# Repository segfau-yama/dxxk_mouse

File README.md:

# dxxk_mouse

ESP32-S3 上で動作する Rust 製 USB 入力デバイスの実験用リポジトリです。

ファームウェアは、USB HID のキーボードとマウス、USB Audio Class 1（UAC1）のマイクとスピーカーを一つの USB デバイスとして提供します。

## 対象環境

| 項目 | 構成 |
| --- | --- |
| MCU | ESP32-S3 |
| Rust target | `xtensa-esp32s3-none-elf` |
| HAL | `esp-hal` |
| async runtime | Embassy、`esp-rtos` |
| USB | `embassy-usb` |
| 実機テスト | `embedded-test`、`probe-rs` |

## ディレクトリ構成

```text
dick_mouse
├── Cargo.toml
├── .cargo/config.toml
├── src
│   ├── main.rs
│   ├── lib.rs
│   ├── device
│   │   ├── button.rs
│   │   ├── encoder.rs
│   │   ├── joystick.rs
│   │   ├── microphone.rs
│   │   └── speaker.rs
│   └── tasks
│       ├── audio.rs
│       ├── hid.rs
│       ├── keyboard.rs
│       ├── mouse.rs
│       └── usb.rs
└── tests
    ├── device
    │   ├── button.rs
    │   ├── encoder.rs
    │   ├── joystick.rs
    │   ├── microphone.rs
    │   └── speaker.rs
    ├── main.rs
    ├── reexports.rs
    └── tasks
        └── mod.rs
```

## 設計図

```mermaid
flowchart TD
  subgraph Mode["mode"]
    direction TB
    UsbHidReports["CHANNEL: USB_HID_REPORTS"]
    ModeGpio["PERIPHERAL: GPIO21 slide switch"] --> HidTask["TASK: hid_task"]
  end

  subgraph Keyboard["keyboard"]
    direction TB
    ShortcutGpio["PERIPHERAL: GPIO6/7 shortcut buttons"]
    PushGpio["PERIPHERAL: GPIO42 joystick push"]
    KeyboardTask["TASK: keyboard_task"]
    KeyboardReports["CHANNEL: KEYBOARD_REPORTS"]
    ShortcutGpio --> KeyboardTask
    PushGpio --> KeyboardTask
  end

  subgraph Mouse["mouse"]
    direction TB
    ClickGpio["PERIPHERAL: GPIO38/39 click buttons"]
    JoystickAdc["PERIPHERAL: ADC1 GPIO1/2 joystick"]
    ScrollPcnt["PERIPHERAL: PCNT0 GPIO11/12 scroll encoder"]
    MouseTask["TASK: mouse_task"]
    MouseReports["CHANNEL: MOUSE_REPORTS"]
    ClickGpio --> MouseTask
    JoystickAdc --> MouseTask
    ScrollPcnt --> MouseTask
  end

  subgraph Microphone["microphone"]
    direction TB
    I2sMic["PERIPHERAL: I2S0 RX microphone"]
    MicMuteGpio["PERIPHERAL: GPIO4 microphone mute"]
    MicVolumePcnt["PERIPHERAL: PCNT1 GPIO13/14 volume encoder"]
    MicrophoneTask["TASK: microphone_task"]
    MicrophoneFrames["SPSC: MICROPHONE_RING"]
    I2sMic --> MicrophoneTask
    MicMuteGpio --> MicrophoneTask
    MicVolumePcnt --> MicrophoneTask
    MicrophoneTask --> MicrophoneFrames
  end

  subgraph Speaker["speaker"]
    direction TB
    SpeakerFrames["SPSC: SPEAKER_RING"]
    SpeakerMuteGpio["PERIPHERAL: GPIO5 speaker mute"]
    SpeakerVolumePcnt["PERIPHERAL: PCNT2 GPIO40/41 volume encoder"]
    SpeakerTask["TASK: speaker_task"]
    I2sSpeaker["PERIPHERAL: I2S0 TX speaker"]
    SpeakerFrames --> SpeakerTask
    SpeakerMuteGpio --> SpeakerTask
    SpeakerVolumePcnt --> SpeakerTask
    SpeakerTask --> I2sSpeaker
  end

  UsbTask["TASK: usb_task"]

  subgraph Usb["usb"]
    direction LR
    UsbHid["USB: HID keyboard / mouse"]
    UsbMic["USB: UAC microphone"]
    UsbSpeaker["USB: UAC speaker"]
    UsbPeripheral["PERIPHERAL: USB0 GPIO19/20"]
    UsbHid --> UsbPeripheral
    UsbMic --> UsbPeripheral
    UsbPeripheral --> UsbSpeaker
  end

  UsbTask --> UsbHid
  UsbTask --> UsbMic
  UsbSpeaker --> UsbTask

  KeyboardTask --> KeyboardReports
  MouseTask --> MouseReports
  KeyboardReports --> HidTask
  MouseReports --> HidTask
  HidTask --> UsbHidReports
  UsbHidReports --> UsbTask
  MicrophoneFrames --> UsbTask
  UsbTask --> SpeakerFrames

  class ShortcutGpio,PushGpio,ModeGpio,ClickGpio,JoystickAdc,ScrollPcnt,MicMuteGpio,MicVolumePcnt,I2sMic,SpeakerMuteGpio,SpeakerVolumePcnt,I2sSpeaker,UsbPeripheral peripheral
  class KeyboardTask,HidTask,MouseTask,MicrophoneTask,SpeakerTask,UsbTask task
  class KeyboardReports,MouseReports,UsbHidReports,MicrophoneFrames,SpeakerFrames channel
  class UsbHid,UsbMic,UsbSpeaker usb

  classDef peripheral fill:#ddf4ff,stroke:#0969da,color:#24292f
  classDef task fill:#dafbe1,stroke:#1a7f37,color:#24292f
  classDef channel fill:#fff8c5,stroke:#9a6700,color:#24292f
  classDef usb fill:#fbefff,stroke:#8250df,color:#24292f
```

## 実装概要

### デバイス状態

| 型 | 入力 | 責務 |
| --- | --- | --- |
| `Button` | GPIO level、時刻 | active level、debounce、押下状態を保持する |
| `RotaryEncoder` | PCNT count、時刻 | count を安定化し、detent 算出に使う値を保持する |
| `Joystick` | X/Y の ADC 値 | 初期位置を中心として X/Y の差分を計算する |
| `Microphone` | I2S RX frame | USB マイクへ送る音声フレームを保持する |
| `Speaker` | USB speaker frame | I2S TX へ送る音声フレームを保持する |

各構造体は setter や `&mut self` を持たず、`update(self) -> Self` または `new()` で新しい状態を返します。

### task のデータフロー

USB HID と USB Audio は、同じ列で入力、処理、出力を示します。

#### USB HID

| task | 入力 | 処理 | 出力 |
| --- | --- | --- | --- |
| `keyboard_task` | joystick push、Back、Forward の GPIO | `Button` を更新し、ボタン状態を集約する | `KEYBOARD_REPORTS` |
| `mouse_task` | click の GPIO、joystick の ADC、encoder の PCNT | `Button`、`Joystick`、`RotaryEncoder` を更新し、マウス入力を集約する | `MOUSE_REPORTS` |
| `hid_task` | mode GPIO、`KEYBOARD_REPORTS`、`MOUSE_REPORTS` | mode に応じて入力を keyboard または mouse report に変換する | `USB_HID_REPORTS` |
| `usb_task` | `USB_HID_REPORTS` | report ID を付けて HID endpoint へ書き込む | USB HID keyboard、mouse |

#### USB Audio

| task | 入力 | 処理 | 出力 |
| --- | --- | --- | --- |
| `microphone_task` | I2S RX、mute GPIO、volume encoder の PCNT | DMAを常時drainし、muteと音量を反映したmono S16を格納する | `MICROPHONE_RING` |
| `usb_task`（microphone） | `MICROPHONE_RING` | リングを待たずに47/48/49 sampleのmono packetを組み立てる | USB UAC1 microphone |
| `usb_task`（speaker） | USB UAC1 speaker | mono S16を格納し、USB mute/volumeも監視する | `SPEAKER_RING` |
| `speaker_task` | `SPEAKER_RING`、mute GPIO、volume encoder の PCNT | USBと物理入力のmute/volumeを反映し、連続DMAへstereo S32を補充する | I2S TX |

## 入力割り当て

`GPIO21` のスライドスイッチに応じて、`hid_task` が通常モードとゲームモードを切り替えます。

| 入力 | 通常モード | ゲームモード |
| --- | --- | --- |
| joystick X/Y | Mouse X/Y | Arrow keys |
| joystick push | PrintScreen | S |
| left click | Mouse left button | A |
| right click | Mouse right button | D |
| Back button | Ctrl+Left | Space |
| Forward button | Ctrl+Right | Enter |
| scroll encoder | Mouse wheel | 使用しない |

ゲームモードでは joystick の X/Y 差分が `512` を超えた方向をキー入力へ変換します。

同時押しが HID keyboard の上限を超えた場合は、実装上の割り当て順で先頭の 6 キーを送信します。

## USB インターフェース

| インターフェース | USB class | 方向 | データ形式 |
| --- | --- | --- | --- |
| Keyboard | HID、report ID `1` | ESP32-S3 から PC | modifier、6 keycodes |
| Mouse | HID、report ID `2` | ESP32-S3 から PC | buttons、X/Y、wheel、pan |
| Microphone | UAC1 source | ESP32-S3 から PC | 48 kHz、16-bit、mono、単一IN、feedbackなし |
| Speaker | UAC1 speaker | PC から ESP32-S3 | 48 kHz、16-bit、mono（Left Front） |

I2S は RX、TX ともに 48 kHz、32-bit slot で動作します。
RX はINMP441の左スロットだけをDMAへ取り込み、符号付き24-bitから16-bit PCMへ変換します（L/R端子はLow）。
TX はUSBのmono S16を32-bitの上位16 bitへ配置し、左右両スロットへ複製します。
マイクは未実装のUSB音量制御を広告せず、スピーカーはUSBのmute/volumeと物理ボタンをPCMへ反映します。
音声にはheaplessのSPSCキューを使用し、USB/I2S処理中にUARTログを出しません。

現在の試作機の配線と再録音の確認方法は [AUDIO_CHECK.md](AUDIO_CHECK.md) を参照してください。
以下の回路設計用ピン表と試作機の `main.rs` は異なるため、配線の変更時には `main.rs` を確認してください。

## ピン割り当て

| 機能 | 信号 | peripheral | GPIO | 所有する task |
| --- | --- | --- | --- | --- |
| Mode | slide switch | GPIO | `GPIO21` | `hid_task` |
| Keyboard | joystick push | GPIO | `GPIO42` | `keyboard_task` |
| Keyboard | Back button | GPIO | `GPIO6` | `keyboard_task` |
| Keyboard | Forward button | GPIO | `GPIO7` | `keyboard_task` |
| Mouse | joystick X | ADC1 | `GPIO1` | `mouse_task` |
| Mouse | joystick Y | ADC1 | `GPIO2` | `mouse_task` |
| Mouse | scroll encoder A | PCNT0 | `GPIO11` | `mouse_task` |
| Mouse | scroll encoder B | PCNT0 | `GPIO12` | `mouse_task` |
| Mouse | left click | GPIO | `GPIO38` | `mouse_task` |
| Mouse | right click | GPIO | `GPIO39` | `mouse_task` |
| Microphone | mute button | GPIO | `GPIO4` | `microphone_task` |
| Microphone | volume encoder A | PCNT1 | `GPIO13` | `microphone_task` |
| Microphone | volume encoder B | PCNT1 | `GPIO14` | `microphone_task` |
| Microphone | BCLK | I2S0 RX | `GPIO15` | `microphone_task` |
| Microphone | WS | I2S0 RX | `GPIO16` | `microphone_task` |
| Microphone | DIN | I2S0 RX | `GPIO17` | `microphone_task` |
| Speaker | mute button | GPIO | `GPIO5` | `speaker_task` |
| Speaker | volume encoder A | PCNT2 | `GPIO40` | `speaker_task` |
| Speaker | volume encoder B | PCNT2 | `GPIO41` | `speaker_task` |
| Speaker | BCLK | I2S0 TX | `GPIO8` | `speaker_task` |
| Speaker | WS | I2S0 TX | `GPIO9` | `speaker_task` |
| Speaker | DOUT | I2S0 TX | `GPIO10` | `speaker_task` |
| USB | D- | USB0 | `GPIO19` | `usb_task` |
| USB | D+ | USB0 | `GPIO20` | `usb_task` |

I2S RX と I2S TX は `I2S0` と `DMA_CH0` を共有します。

マイクとスピーカーの音量は起動時を 100% とし、エンコーダーの 1 detent ごとに 5% ずつ、0% から 100% の範囲で変更します。

`GPIO0/3/45/46` は strapping、`GPIO43/44` は UART0、`GPIO19/20` は USB に使われるため、汎用入力には割り当てていません。

`GPIO39/40/41/42` は外部 JTAG の既定信号と重なるため、現在の入力配線と外部 JTAG は同時に使用できません。

## ビルドと書き込み

```sh
cd dick_mouse
cargo check
cargo run --release
```

通常実行時の runner は `.cargo/config.toml` に定義した `espflash flash` です。

## 実機テスト

テストはホスト PC 上の unit test ではなく、ESP32-S3 実機上で動作する `embedded-test` 形式です。

```sh
cargo test-hil
```

`cargo test-hil` は `.cargo/config.toml` の alias で、runner を `probe-rs run --chip esp32s3` に上書きします。

| test target | 検証対象 |
| --- | --- |
| `button` | debounce と押下状態 |
| `encoder` | count の安定化 |
| `joystick` | 中心位置からの X/Y 差分 |
| `microphone` | microphone frame の状態型 |
| `speaker` | speaker frame の状態型 |
| `reexports` | `device` 型の公開 API |
| `tasks` | PCM 変換、HID report 変換、task の入口 |
| `main` | firmware で使う peripheral の初期化 |

`tests/` 配下の各ファイルは `Cargo.toml` の `[[test]]` で明示し、ESP32-S3 上の結合テストとして実行します。

## 制約

- ビルドには `xtensa-esp32s3-none-elf` target に対応した Rust 環境が必要です。
- 実機テストには `probe-rs` がデバイスへアクセスできる権限が必要です。
- `embassy-usb` は UAC1 source を使うため、Embassy の git revision に固定しています。

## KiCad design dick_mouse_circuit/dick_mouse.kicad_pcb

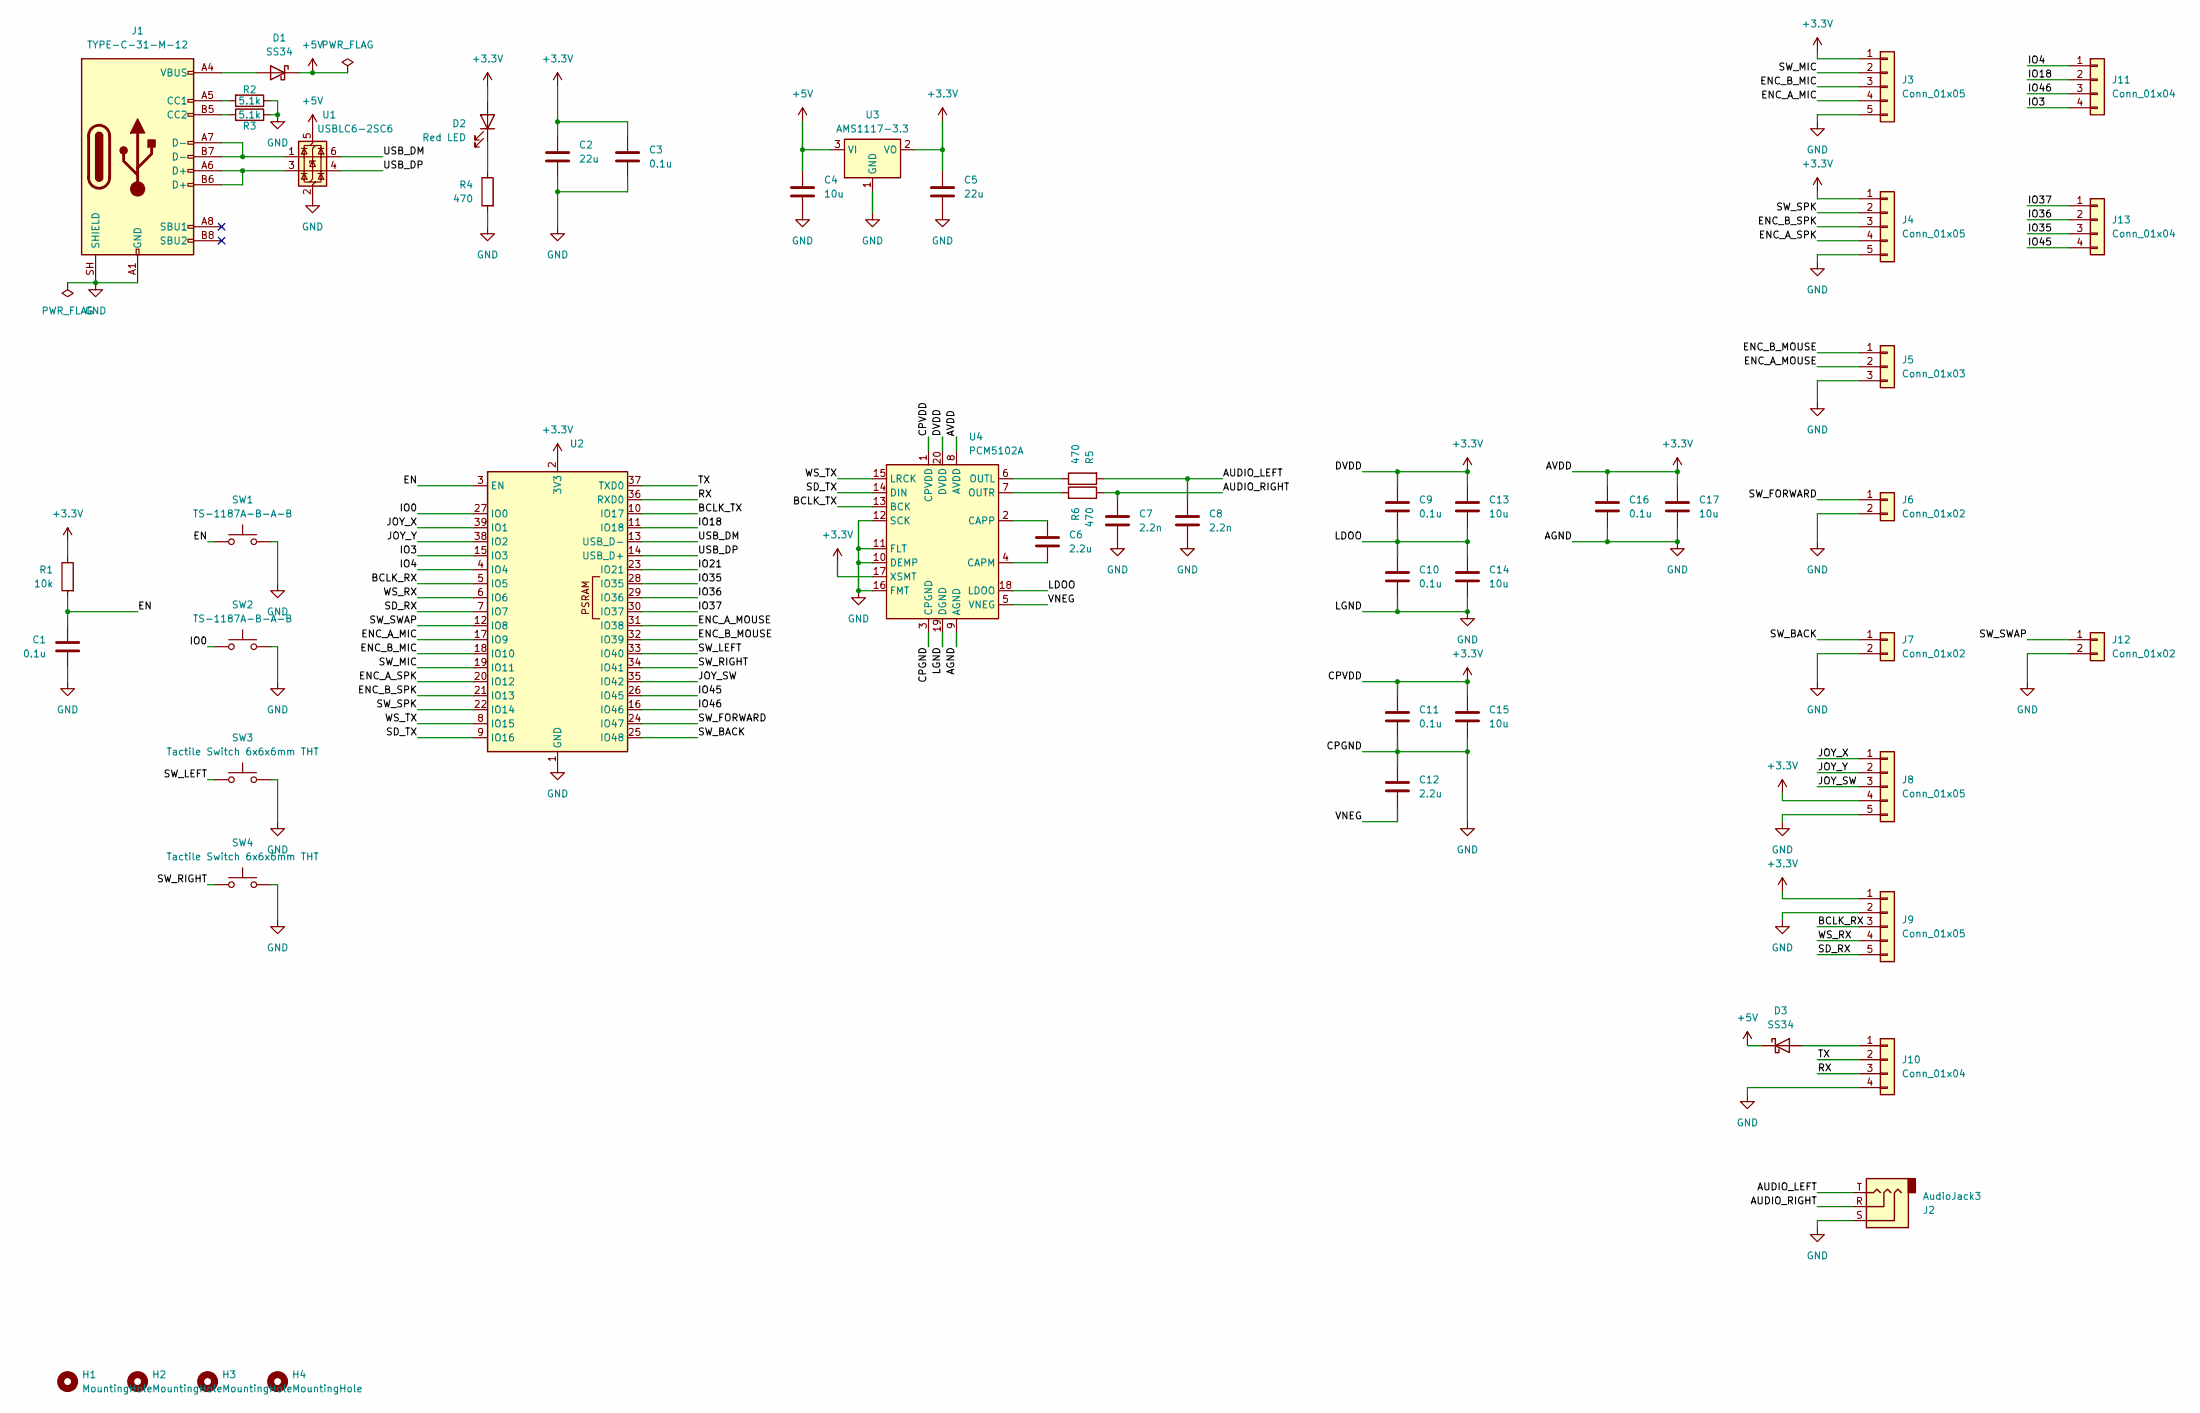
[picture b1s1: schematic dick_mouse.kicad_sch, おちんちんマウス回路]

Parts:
C1, C3, C9, C10, C11, C16: 0.1u; C_0402_1005Metric; MPN CL05B104KO5NNNC; LCSC C1525
C2, C5: 22u; C_0805_2012Metric; MPN CL21A226MAQNNNE; LCSC C45783
C4, C13, C14, C15, C17: 10u; C_0603_1608Metric; MPN CL10A106MA8NRNC; LCSC C96446
C6, C12: 2.2u; C_0402_1005Metric; MPN CL05A225MQ5NSNC; LCSC C12530
C7, C8: 2.2n; C_0402_1005Metric; MPN 0402B222K500NT; LCSC C1531
D1, D3: SS34; D_SMA; MPN SS34; LCSC C8678
D2: Red LED; LED_0603_1608Metric; MPN KT-0603R; LCSC C2286
H1, H2, H3, H4: MountingHole; MountingHole_3.2mm_M3
J1: TYPE-C-31-M-12; USB_C_Receptacle_HRO_TYPE-C-31-M-12; MPN TYPE-C-31-M-12; LCSC C165948
J2: AudioJack3; C668608_PJ-313D; MPN PJ-313D; LCSC C668608
J3, J4, J8, J9: Conn_01x05; JST_XH_B5B-XH-A_1x05_P2.50mm_Vertical; MPN PZ254V-11-05P; LCSC C492404
J5: Conn_01x03; JST_XH_B3B-XH-A_1x03_P2.50mm_Vertical; MPN PZ254V-11-03P; LCSC C2937625
J6, J7, J12: Conn_01x02; JST_XH_B2B-XH-A_1x02_P2.50mm_Vertical; MPN PZ254V-11-02P; LCSC C492401
J10, J11, J13: Conn_01x04; PinHeader_1x04_P2.54mm_Vertical; MPN PZ254V-11-04P; LCSC C2691448
R1: 10k; R_0402_1005Metric; MPN 0402WGF1002TCE; LCSC C25744
R2, R3: 5.1k; R_0402_1005Metric; MPN 0402WGF5101TCE; LCSC C25905
R4, R5, R6: 470; R_0402_1005Metric; MPN 0402WGF4700TCE; LCSC C25117
SW1, SW2: TS-1187A-B-A-B; SW_Push_1P1T_XKB_TS-1187A; MPN TS-1187A-B-A-B; LCSC C318884
SW3, SW4: Tactile Switch 6x6x6mm THT; SW_PUSH_6mm
U1: USBLC6-2SC6; SOT-23-6
U2: ESP32-S3-WROOM-1
U3: AMS1117-3.3; SOT-223-3_TabPin2; MPN AMS1117-3.3; LCSC C6186
U4: PCM5102A; TSSOP-20_4.4x6.5mm_P0.65mm

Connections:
+3.3V: C2.1, C3.1, C5.1, C9.1, C11.1, C13.1, C15.1, C16.1, C17.1, D2.2 (A), J3.1, J4.1, J8.4, J9.1, R1.1, U2.2 (3V3), U3.2 (VO), U4.1 (CPVDD), U4.8 (AVDD), U4.17 (XSMT), U4.20 (DVDD)
+5V: C4.1, D1.1 (K), D3.1 (K), U1.5 (VBUS), U3.3 (VI)
/AUDIO_LEFT: C8.1, J2.T, R5.2
/AUDIO_RIGHT: C7.1, J2.R, R6.1
/BCLK_RX: J9.3, U2.5 (IO5)
/BCLK_TX: U2.10 (IO17), U4.13 (BCK)
/EN: C1.1, R1.2, SW1.1, U2.3 (EN)
/ENC_A_MIC: J3.4, U2.17 (IO9)
/ENC_A_MOUSE: J5.2, U2.31 (IO38)
/ENC_A_SPK: J4.4, U2.20 (IO12)
/ENC_B_MIC: J3.3, U2.18 (IO10)
/ENC_B_MOUSE: J5.1, U2.32 (IO39)
/ENC_B_SPK: J4.3, U2.21 (IO13)
/IO0: SW2.1, U2.27 (IO0)
/IO3: J11.4, U2.15 (IO3)
/IO4: J11.1, U2.4 (IO4)
/IO18: J11.2, U2.11 (IO18)
/IO21: U2.23 (IO21)
/IO35: J13.3, U2.28 (IO35)
/IO36: J13.2, U2.29 (IO36)
/IO37: J13.1, U2.30 (IO37)
/IO45: J13.4, U2.26 (IO45)
/IO46: J11.3, U2.16 (IO46)
/JOY_SW: J8.3, U2.35 (IO42)
/JOY_X: J8.1, U2.39 (IO1)
/JOY_Y: J8.2, U2.38 (IO2)
/LDOO: C9.2, C10.1, C13.2, C14.1, U4.18 (LDOO)
/RX: J10.3, U2.36 (RXD0)
/SD_RX: J9.5, U2.7 (IO7)
/SD_TX: U2.9 (IO16), U4.14 (DIN)
/SW_BACK: J7.1, U2.25 (IO48)
/SW_FORWARD: J6.1, U2.24 (IO47)
/SW_LEFT: SW3.1, U2.33 (IO40)
/SW_MIC: J3.2, U2.19 (IO11)
/SW_RIGHT: SW4.1, U2.34 (IO41)
/SW_SPK: J4.2, U2.22 (IO14)
/SW_SWAP: J12.1, U2.12 (IO8)
/TX: J10.2, U2.37 (TXD0)
/USB_DM: U1.6 (I/O1), U2.13 (USB_D-)
/USB_DP: U1.4 (I/O2), U2.14 (USB_D+)
/VNEG: C12.2, U4.5 (VNEG)
/WS_RX: J9.4, U2.6 (IO6)
/WS_TX: U2.8 (IO15), U4.15 (LRCK)
GND: C1.2, C2.2, C3.2, C4.2, C5.2, C7.2, C8.2, C10.2, C11.2, C12.1, C14.2, C15.2, C16.2, C17.2, J1.A1 (GND), J1.A12 (GND), J1.B1 (GND), J1.B12 (GND), J1.SH (SHIELD), J2.S, J3.5, J4.5, J5.3, J6.2, J7.2, J8.5, J9.2, J10.4, J12.2, R2.1, R3.1, R4.2, SW1.2, SW2.2, SW3.2, SW4.2, U1.2 (GND), U2.1 (GND), U2.40 (GND), U2.41 (GND), U3.1 (GND), U4.3 (CPGND), U4.9 (AGND), U4.10 (DEMP), U4.11 (FLT), U4.12 (SCK), U4.16 (FMT), U4.19 (DGND)
unnamed: D1.2 (A), J1.A4 (VBUS), J1.A9 (VBUS), J1.B4 (VBUS), J1.B9 (VBUS)
unnamed: D2.1 (K), R4.1
unnamed: D3.2 (A), J10.1
unnamed: J1.A5 (CC1), R2.2
unnamed: J1.B5 (CC2), R3.2
unnamed: J1.A6 (D+), J1.B6 (D+), U1.3 (I/O2)
unnamed: J1.A7 (D-), J1.B7 (D-), U1.1 (I/O1)
unnamed: C6.2, U4.4 (CAPM)
unnamed: C6.1, U4.2 (CAPP)
unnamed: R5.1, U4.6 (OUTL)
unnamed: R6.2, U4.7 (OUTR)

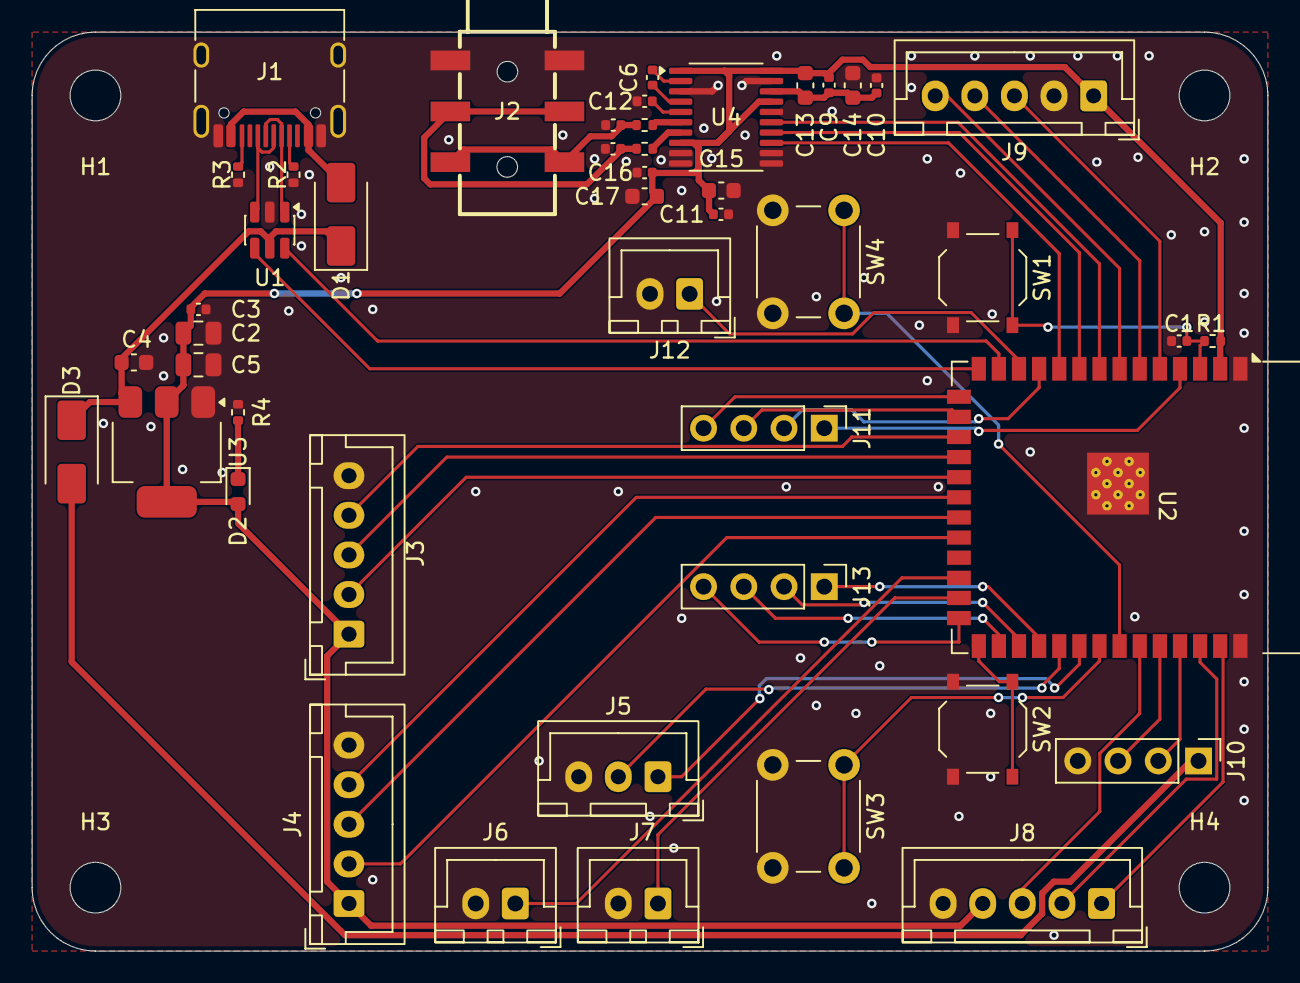
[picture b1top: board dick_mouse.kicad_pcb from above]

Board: 2 copper layers, 78.0 x 58.0 mm, 51 parts (0 on the bottom side), 54 nets.
